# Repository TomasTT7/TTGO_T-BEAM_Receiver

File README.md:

# TTGO T-BEAM Receiver
This is the main repository for a TTGO T-BEAM based receiver.

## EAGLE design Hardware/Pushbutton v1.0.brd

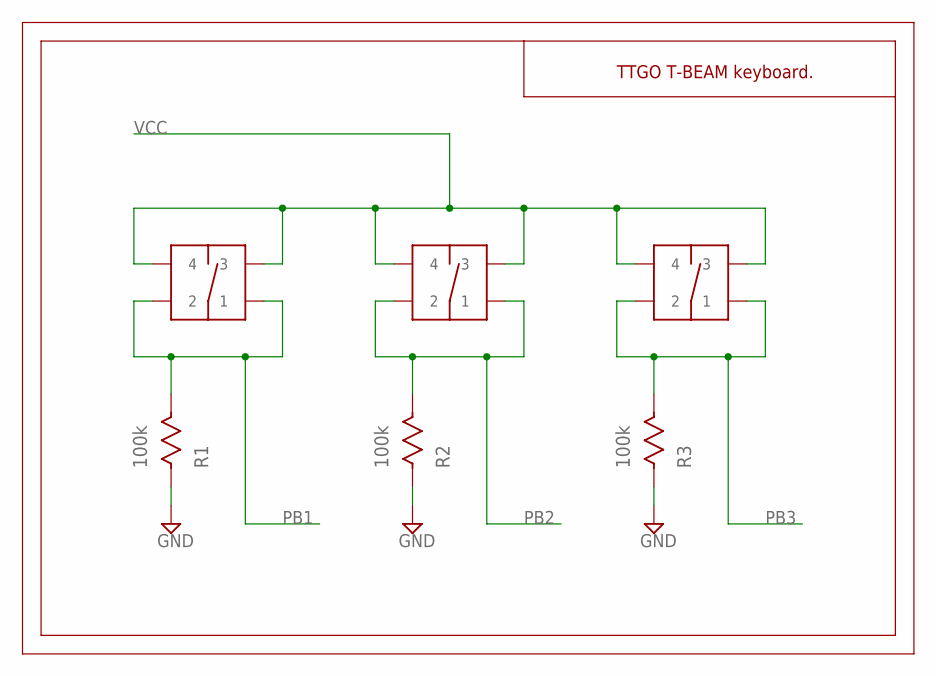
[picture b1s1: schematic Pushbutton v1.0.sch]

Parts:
B1, B2, B3: PUSHBUTTON_1
R1, R2, R3: 100k; RES0402

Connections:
GND: R1.P$1, R2.P$1, R3.P$1
PB1: B1.1, B1.2, R1.P$2
PB2: B2.1, B2.2, R2.P$2
PB3: B3.1, B3.2, R3.P$2
VCC: B1.3, B1.4, B2.3, B2.4, B3.3, B3.4

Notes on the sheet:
TTGO T-BEAM keyboard.

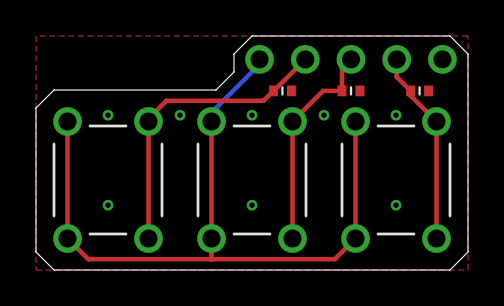
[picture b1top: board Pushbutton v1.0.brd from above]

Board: 2 copper layers, 24.0 x 13.0 mm, 6 parts (0 on the bottom side), 5 nets.

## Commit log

2019-11-29 Create temp
